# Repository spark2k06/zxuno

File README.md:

# loader128k y 128sna2rom

Cargador de "ROMs" para ZXUno a partir snapshots de 128K, para utilizar desde el menú del firmware. 

Por un lado tenemos el cargador loader128k, que se autocopia en la VRAM para despues pasar el control al mismo. 

Desde la VRAM se mueven todos los bloques de 16Kb al lugar que les corresponde, se restauran los registros y por último se 

pasa el control al PC del Snapshot.

128sna2rom por su parte se utiliza para crear la "ROM" parcheando datos de loader128k.

Idea desarrollada a partir del siguiente hilo con ayuda de Antonio Villena y el emulador ZEsarUX de Cesar Hernández:

http://www.zxuno.com/forum/viewtopic.php?f=12&t=530

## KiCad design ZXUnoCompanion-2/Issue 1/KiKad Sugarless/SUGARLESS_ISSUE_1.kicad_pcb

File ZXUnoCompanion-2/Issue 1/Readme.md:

Propuestas para una hipotética Issue 2, para quién se atreva con ella :-):

- LLevar todos los pines disponibles de Atmega128 o Arduino Mega 2560 a un único conector, a modo de expansión.

- Corregir pinout ISP del atmega128 para evitar tener que hacer fix si se quiere usar éste. Se trata de los pines MOSI y MISO, que actualmente no están donde corresponden.

- Añadir chip CH340 para poder programar el atmega128 por serie como la versión del arduino mega, en lugar de sólo por ISP, y llevar pos pistas las señales del CH340 a los pines D+ y D- del conector de arduino, para que también pueda ser programado desde el conector microUSB sin necesidad de abrir la carcasa.

- ¿Otras?

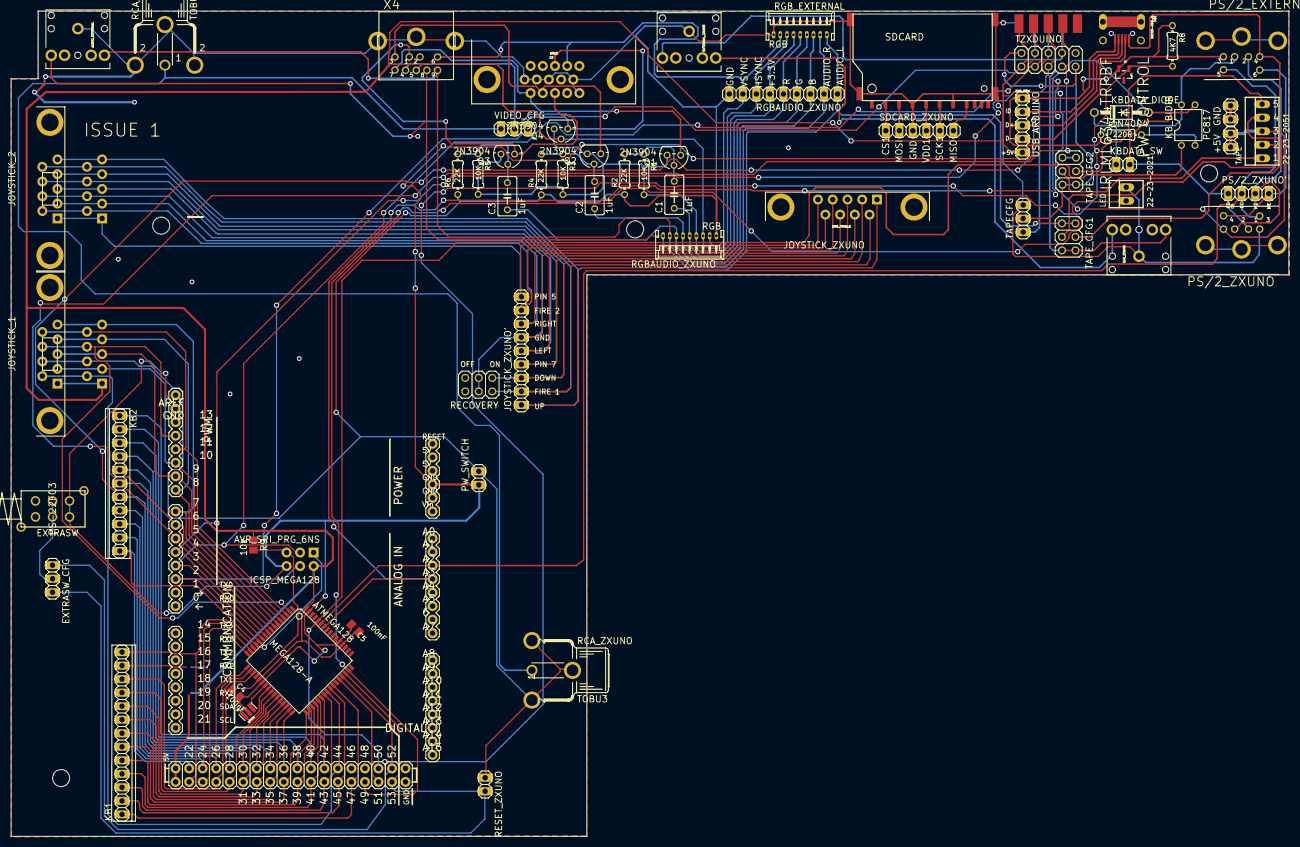
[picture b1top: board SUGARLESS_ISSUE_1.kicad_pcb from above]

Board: 2 copper layers, 240.0 x 155.0 mm, 68 parts (0 on the bottom side), 98 nets.

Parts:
+5V: 1X02
@HOLE0, @HOLE1, @HOLE2, @HOLE3: (no value)
ARDUINO_MEGA: ARDUINO_MEGA_R3FULL; ARDUINO_MEGA
ATMEGA128: MEGA128-A; TQFP64
AUDIO_EXTERNAL: AUDIO-JACK
C1, C2, C3: 1uF; C050-035X075
C4, C5: 100nF; C0805K
EAR_ZXUNO: AUDIO-JACK
EXTERNAL_ZXUNO: AUDIO-JACK
EXTRASW: PS-22F03
EXTRASW_CFG: 1X03
GND: 1X02
ICSP_MEGA128: AVR_SPI_PRG_6NS; 2X3-NS
JOYSTICK_1, JOYSTICK_2: DB9_MALE
JOYSTICK_ZXUNO: DB9_FEMALE; DB9
JOYSTICK_ZXUNO': 1X09
KB1: 1X13
KB2: 1X11
KBDATA_DIODE: 1N4004; DO41-10
KBDATA_SW: 1X02
KB_BIDIR: PC817; DIL04
LED: 22-23-2021
PS/2_EXTERNAL, PS/2_ZXUNO: M_DIN6
PS/2_ZXUNO': 1X04
PW_CONTROL: IRLML6344TRPBF; SOT95P240X112-3N
PW_SWITCH: 1X02
Q1, Q2, Q3, Q4: 2N3904; TO92
R1, R3, R5: 10K; 0204%2f7
R2, R4, R6: 22K; 0204%2f7
R7: 220R; 0204%2f7
R8: 4K7; 0204%2f7
R9: 10k; M0805
RCA_EXTERNAL: TOBU3
RCA_ZXUNO: TOBU3
RECOVERY: 2X03
RESET_ZXUNO: 1X02
RGBAUDIO_ZXUNO: RGB; 53048-09
RGBAUDIO_ZXUNO': 1X09
RGB_EXTERNAL: RGB; 53048-09
SDCARD: SDCMF-10915W010
SDCARD_ZXUNO: 1X06
TAPE: 22-23-2051
TAPECFG: 1X03
TAPE_CFG1, TAPE_CFG2: 2X03
TZXDUINO: 2X05
U$1: MICRO-USB-B; MICRO_USB_4_LEGS
USB_ARDUINO: 1X05
VIDEO_CFG: 1X03
X3: DB15
X4: M_DIN9
X5: F09D
Y1: 16MHz; RESONATOR

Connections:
+3.3V: Q1.1, Q2.1, Q3.1, Q4.1, R1.2, R3.2, R5.2, RGBAUDIO_ZXUNO.6, RGBAUDIO_ZXUNO'.6, RGB_EXTERNAL.6
+5V: +5V.1, +5V.2, ARDUINO_MEGA.5V@1, ARDUINO_MEGA.5V@2, ATMEGA128.21, ATMEGA128.52, ATMEGA128.64, C4.1, C5.1, ICSP_MEGA128.2, JOYSTICK_1.5, JOYSTICK_1.14, PS/2_EXTERNAL.4, PS/2_ZXUNO.4, R9.1, TAPE.3, TZXDUINO.1, U$1.VCC, USB_ARDUINO.5, X4.2, X5.1
AUDIO_L: AUDIO_EXTERNAL.TIP, RGBAUDIO_ZXUNO.1, RGBAUDIO_ZXUNO'.1, RGB_EXTERNAL.1, TAPE_CFG1.1, TAPE_CFG1.2, X4.8
AUDIO_R: AUDIO_EXTERNAL.RING, RGBAUDIO_ZXUNO.2, RGBAUDIO_ZXUNO'.2, RGB_EXTERNAL.2, X4.9
B: C3.1, RGBAUDIO_ZXUNO.3, RGBAUDIO_ZXUNO'.3, RGB_EXTERNAL.3
BOUT: Q3.3, X3.3, X4.1
COMPOSITE: RCA_EXTERNAL.1, RCA_ZXUNO.1, VIDEO_CFG.1
CS1: SDCARD.1, SDCARD_ZXUNO.1
CSYNC: Q4.3, VIDEO_CFG.3, X3.13
D+: U$1.D+, USB_ARDUINO.3
D-: U$1.D-, USB_ARDUINO.4
EXTRA: ARDUINO_MEGA.52, ATMEGA128.45, EXTRASW_CFG.1
G: C2.1, RGBAUDIO_ZXUNO.4, RGBAUDIO_ZXUNO'.4, RGB_EXTERNAL.4
GND: GND.1, GND.2, JOYSTICK_1.8, JOYSTICK_1.17, LED.2, PS/2_ZXUNO.3, PW_CONTROL.3, PW_SWITCH.2, R2.1, R4.1, R6.1, RCA_EXTERNAL.2, RCA_EXTERNAL.2@1, RCA_EXTERNAL.2@2, RCA_ZXUNO.2, RCA_ZXUNO.2@1, RCA_ZXUNO.2@2, RESET_ZXUNO.1, RGBAUDIO_ZXUNO.9, RGBAUDIO_ZXUNO'.9, RGB_EXTERNAL.9, SDCARD.3, SDCARD.6, SDCARD.M1, SDCARD.M2, SDCARD.M3, SDCARD.M4, SDCARD_ZXUNO.3, TAPECFG.3, X3.5, X3.6, X3.7, X3.8, X3.10, X4.SH1, X4.SH2, X4.SH3, X5.5, X5.6
GND_POW: ATMEGA128.22, ATMEGA128.53, ATMEGA128.63, C4.2, C5.2, EXTRASW.5, EXTRASW.6, ICSP_MEGA128.6, PS/2_EXTERNAL.3, PW_CONTROL.2, PW_SWITCH.1, R7.1, R8.1, TAPECFG.1, U$1.GND, USB_ARDUINO.1, Y1.2
GND_TAPE: TAPECFG.2, TAPE_CFG2.5, TAPE_CFG2.6, TZXDUINO.2, TZXDUINO.9
GOUT: Q2.3, X3.2, X4.3
HSYNC: Q4.2, RGBAUDIO_ZXUNO.7, RGBAUDIO_ZXUNO'.7, RGB_EXTERNAL.7, X4.5
ID: U$1.ID, USB_ARDUINO.2
IN_L: EAR_ZXUNO.TIP, EXTERNAL_ZXUNO.TIP, TAPE_CFG1.5, TAPE_CFG1.6, TZXDUINO.8, X5.9
IN_R: EAR_ZXUNO.RING, EXTERNAL_ZXUNO.RING
JOY2PS2_1: ARDUINO_MEGA.7, ATMEGA128.7, JOYSTICK_1.1, JOYSTICK_1.10
JOY2PS2_2: ARDUINO_MEGA.8, ATMEGA128.6, JOYSTICK_1.2, JOYSTICK_1.11
JOY2PS2_3: ARDUINO_MEGA.9, ATMEGA128.5, JOYSTICK_1.3, JOYSTICK_1.12
JOY2PS2_4: ARDUINO_MEGA.10, ATMEGA128.4, JOYSTICK_1.4, JOYSTICK_1.13
JOY2PS2_6: ARDUINO_MEGA.11, ATMEGA128.3, JOYSTICK_1.6, JOYSTICK_1.15
JOY2PS2_7: ARDUINO_MEGA.12, ATMEGA128.2, JOYSTICK_1.7, JOYSTICK_1.16
JOY2PS2_9: ARDUINO_MEGA.44, ATMEGA128.40, JOYSTICK_1.9, JOYSTICK_1.18
JOYZXUNO_1: JOYSTICK_2.1, JOYSTICK_2.10, JOYSTICK_ZXUNO.1, JOYSTICK_ZXUNO'.1
JOYZXUNO_2: JOYSTICK_2.2, JOYSTICK_2.11, JOYSTICK_ZXUNO.2, JOYSTICK_ZXUNO'.3, RECOVERY.1
JOYZXUNO_3: JOYSTICK_2.3, JOYSTICK_2.12, JOYSTICK_ZXUNO.3, JOYSTICK_ZXUNO'.5
JOYZXUNO_4: JOYSTICK_2.4, JOYSTICK_2.13, JOYSTICK_ZXUNO.4, JOYSTICK_ZXUNO'.7
JOYZXUNO_5: JOYSTICK_2.5, JOYSTICK_2.14, JOYSTICK_ZXUNO.5, JOYSTICK_ZXUNO'.9
JOYZXUNO_6: JOYSTICK_2.6, JOYSTICK_2.15, JOYSTICK_ZXUNO.6, JOYSTICK_ZXUNO'.2, RECOVERY.2
JOYZXUNO_7: JOYSTICK_2.7, JOYSTICK_2.16, JOYSTICK_ZXUNO.7, JOYSTICK_ZXUNO'.4
JOYZXUNO_8: JOYSTICK_2.8, JOYSTICK_2.17, JOYSTICK_ZXUNO.8, JOYSTICK_ZXUNO'.6, RECOVERY.3, RECOVERY.4
JOYZXUNO_9: JOYSTICK_2.9, JOYSTICK_2.18, JOYSTICK_ZXUNO.9, JOYSTICK_ZXUNO'.8
KB_CONTROL: ARDUINO_MEGA.50, ATMEGA128.60, KB_BIDIR.1
M1_KB1: ARDUINO_MEGA.23, ATMEGA128.14, KB1.13
M1_KB2: ARDUINO_MEGA.25, ATMEGA128.16, KB1.12
M1_KB3: ARDUINO_MEGA.27, ATMEGA128.18, KB1.11
M1_KB4: ARDUINO_MEGA.29, ATMEGA128.25, KB1.10
M1_KB5: ARDUINO_MEGA.31, ATMEGA128.27, KB1.9
M1_KB6: ARDUINO_MEGA.33, ATMEGA128.29, KB1.8
M1_KB7: ARDUINO_MEGA.35, ATMEGA128.31, KB1.7
M1_KB8: ARDUINO_MEGA.37, ATMEGA128.33, KB1.6
M1_KB9: ARDUINO_MEGA.39, ATMEGA128.35, KB1.5
M1_KB10: ARDUINO_MEGA.41, ATMEGA128.37, KB1.4
M1_KB11: ARDUINO_MEGA.43, ATMEGA128.39, KB1.3
M1_KB12: ARDUINO_MEGA.45, ATMEGA128.41, KB1.2
M1_KB13: ARDUINO_MEGA.47, ATMEGA128.42, KB1.1
M2_KB1: ARDUINO_MEGA.22, ATMEGA128.13, ICSP_MEGA128.1, KB2.11
M2_KB2: ARDUINO_MEGA.24, ATMEGA128.15, KB2.10
M2_KB3: ARDUINO_MEGA.26, ATMEGA128.17, KB2.9
M2_KB4: ARDUINO_MEGA.28, ATMEGA128.19, KB2.8
M2_KB5: ARDUINO_MEGA.30, ATMEGA128.26, KB2.7
M2_KB6: ARDUINO_MEGA.32, ATMEGA128.28, KB2.6
M2_KB7: ARDUINO_MEGA.34, ATMEGA128.30, KB2.5
M2_KB8: ARDUINO_MEGA.36, ATMEGA128.32, KB2.4
M2_KB9: ARDUINO_MEGA.38, ATMEGA128.34, KB2.3
M2_KB10: ARDUINO_MEGA.40, ATMEGA128.36, KB2.2
M2_KB11: ARDUINO_MEGA.42, ATMEGA128.38, KB2.1
MISO1: SDCARD.7, SDCARD_ZXUNO.6
MOSI1: SDCARD.2, SDCARD_ZXUNO.2
unnamed: VIDEO_CFG.2, X4.4
unnamed: PS/2_ZXUNO.SH1, PS/2_ZXUNO.SH2, PS/2_ZXUNO.SH3
unnamed: PS/2_EXTERNAL.SH1, PS/2_EXTERNAL.SH2, PS/2_EXTERNAL.SH3
unnamed: C1.2, Q1.2, R1.1, R2.2
unnamed: KB_BIDIR.2, R7.2
unnamed: ATMEGA128.23, Y1.3
unnamed: ATMEGA128.24, Y1.1
unnamed: C3.2, Q3.2, R5.1, R6.2
unnamed: C2.2, Q2.2, R3.1, R4.2
N/C: TAPE_CFG2.1, TAPE_CFG2.2
PS2_KBCLK: ARDUINO_MEGA.A2, ATMEGA128.59, PS/2_EXTERNAL.5, PS/2_ZXUNO.5, PS/2_ZXUNO'.2
PS2_KBDATA: ARDUINO_MEGA.A3, ATMEGA128.58, KBDATA_DIODE.A, KBDATA_SW.2, KB_BIDIR.3, PS/2_ZXUNO.1, PS/2_ZXUNO'.1
PS2_KBDATA': KBDATA_DIODE.C, KBDATA_SW.1, KB_BIDIR.4, PS/2_EXTERNAL.1
PS2_MSCLK: PS/2_EXTERNAL.6, PS/2_ZXUNO.6, PS/2_ZXUNO'.4
PS2_MSDATA: PS/2_EXTERNAL.2, PS/2_ZXUNO.2, PS/2_ZXUNO'.3
PW_CONTROL: ARDUINO_MEGA.51, ATMEGA128.44, PW_CONTROL.1, R8.2
PW_LED: ARDUINO_MEGA.49, ATMEGA128.47, LED.1
R: C1.1, RGBAUDIO_ZXUNO.5, RGBAUDIO_ZXUNO'.5, RGB_EXTERNAL.5
RESET: ARDUINO_MEGA.53, ATMEGA128.46, EXTRASW_CFG.3, RESET_ZXUNO.2
ROUT: Q1.3, X3.1, X4.7
RST: ATMEGA128.20, ICSP_MEGA128.5, R9.2
SCK1: SDCARD.5, SDCARD_ZXUNO.5
SWITCH: EXTRASW.3, EXTRASW.4, EXTRASW_CFG.2
TAPE_1: TAPE.1, TAPE_CFG2.3
TAPE_2: TAPE.2, TAPE_CFG1.3
TAPE_4: TAPE.4, TAPE_CFG1.4
TAPE_5: TAPE.5, TAPE_CFG2.4
TZX_DOWN: ARDUINO_MEGA.4, ATMEGA128.10, TZXDUINO.5, X5.3
TZX_PLAY: ARDUINO_MEGA.5, ATMEGA128.9, TZXDUINO.6, X5.8
TZX_ROOT: ARDUINO_MEGA.2, ATMEGA128.12, ICSP_MEGA128.4, TZXDUINO.3, X5.2
TZX_STOP: ARDUINO_MEGA.6, ATMEGA128.8, TZXDUINO.7, X5.4
TZX_UP: ARDUINO_MEGA.3, ATMEGA128.11, ICSP_MEGA128.3, TZXDUINO.4, X5.7
VDD1: SDCARD.4, SDCARD_ZXUNO.4
VSYNC: RGBAUDIO_ZXUNO.8, RGBAUDIO_ZXUNO'.8, RGB_EXTERNAL.8, X3.14, X4.6

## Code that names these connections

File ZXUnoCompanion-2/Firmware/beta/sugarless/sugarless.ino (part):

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void TZXDUINO_pushbutton(uint8_t pin, uint8_t bcd)
{
	// Pulsa
	pinPut(TZX_ROOT_PIN, TZX_ROOT_BCD, LO);
	pinSet(TZX_ROOT_PIN, TZX_ROOT_BCD, _OUT);
	
	// Delay de 250 ms
	_delay_ms(250);

	// Suelta
	pinSet(TZX_ROOT_PIN, TZX_ROOT_BCD, _IN);
	pinPut(TZX_ROOT_PIN, TZX_ROOT_BCD, HI);

}

//Inicializar TZXDUINO
void TZXDUINOInit()
{
	pinSet(TZX_ROOT_PIN, TZX_ROOT_BCD, _IN);
	pinPut(TZX_ROOT_PIN, TZX_ROOT_BCD, HI);

	pinSet(TZX_UP_PIN, TZX_UP_BCD, _IN);
	pinPut(TZX_UP_PIN, TZX_UP_BCD, HI);

	pinSet(TZX_DOWN_PIN, TZX_DOWN_BCD, _IN);
	pinPut(TZX_DOWN_PIN, TZX_DOWN_BCD, HI);

	pinSet(TZX_PLAY_PIN, TZX_PLAY_BCD, _IN);
	pinPut(TZX_PLAY_PIN, TZX_PLAY_BCD, HI);

	pinSet(TZX_STOP_PIN, TZX_STOP_BCD, _IN);
	pinPut(TZX_STOP_PIN, TZX_STOP_BCD, HI);
}

//Inicializar Matriz
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
	fnpulsada = 0; //Se pone a 0 la pulsacion de una tecla de funcion
	
	if (pinStat(SYSTEM_PIN, SYSTEM_BCD)) // Gestion del switch SYSTEM (RESET)
	{
		_delay_us(10); //debounce
		if (pinStat(SYSTEM_PIN, SYSTEM_BCD))
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		
		if (matriz[Z_V_ROW][C_COL] & 0x01) // UP
		{
			TZXDUINO_pushbutton(TZX_UP_PIN, TZX_UP_BCD); 
			matriz[Z_V_ROW][C_COL] = 0;
		}

		if (matriz[Z_V_ROW][V_COL] & 0x01) // DOWN
		{
			TZXDUINO_pushbutton(TZX_DOWN_PIN, TZX_DOWN_BCD);
			matriz[Z_V_ROW][V_COL] = 0;
		}

		if (matriz[B_M_ROW][B_COL] & 0x01) // STOP
		{
			TZXDUINO_pushbutton(TZX_STOP_PIN, TZX_STOP_BCD);
			matriz[B_M_ROW][B_COL] = 0;
		}

		if (matriz[B_M_ROW][N_COL] & 0x01) // PLAY
		{
			TZXDUINO_pushbutton(TZX_PLAY_PIN, TZX_PLAY_BCD);
			matriz[B_M_ROW][N_COL] = 0;
		}

		if (matriz[B_M_ROW][M_COL] & 0x01) // ROOT
		{
			TZXDUINO_pushbutton(TZX_ROOT_PIN, TZX_ROOT_BCD);
			matriz[B_M_ROW][M_COL] = 0;
		}

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
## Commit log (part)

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2018-02-24 Issue 1
2018-03-02 Release 7
2018-03-02 Alpha 1
2018-03-10 Alpha 2
2018-03-14 Alpha 3
2018-03-21 Alpha 4
2018-03-28 Beta 1
2018-04-03 Beta 2
2018-04-09 Beta 3
2018-04-10 Beta 4
2018-04-12 Infografia por yoxxxoy
    Infografía de la configuracion de Jumpers por yoxxxoy.
2018-04-12 Infografía por yoxxxoy.
    Infografía de la configuracion de Jumpers por yoxxxoy.
2018-04-12 Infografía por yoxxxoy
    Infografía de la configuracion de Jumpers por yoxxxoy
2018-05-02 Beta 5
2018-05-09 Release 1
2018-05-09 Release 7.1
2018-05-14 Release 1.1
2018-10-08 Release 7.1.1
    Le faltaba un } al último else de la función de setup(), gracias iturbez del foro de zxuno por el aviso.
2018-11-21 Limpieza de repositorio
2018-11-21 Reorganizacion de repositorio
2019-01-12 Release 2
2019-04-20 Release 8
2021-05-19 1.1
    Deteccion correcta la SRAM de 1024KB
2021-05-23 Opción de monocromo (Verde, ámbar y B&W)
2021-05-31 Cambio de paleta monocromática
    Se cambia la paleta de tonalidades monocromáticas para representar mejor los colores brillantes, gracias @desUBIKado por la sugerencia.
2021-06-06 Version alternativa para memoria SRAM externa
    Para sintetizar, adicionalmente se debe deshabilitar los modulos WiFi y MIDI desde el fichero de configuracion common/config.vh
2021-06-08 SAA1099, Control WiFi y Turbo
    Se añade SAA1099, gracias a azesmbog
    Se controla el encendido y apagado de WiFi con F11
    La activación y desactivación del modo Turbo (28 Mhz) con F12 ahora se produce al soltar la tecla, y se mantiene el estado
2021-06-09 SAA1099 y PZX, sin WiFi ni MIDI para SRAM interna
2021-06-09 Opcion de monocromo como modulo opcional
2021-06-13 PZX Loader: Añadir funcionalidad de marca de usuario y rebobinado a esa marca (Contador a 0)
2021-06-13 Cambiado a CTRL-F8 para rewind de fichero y restaurado F9 para STOP
2021-06-13 Actualización de binarios
2021-06-13 Añado la licencia correspondiente
2021-06-21 Version para ZXUncore
    Uso de RGB666 para mejora de la opción monocromática. Ahora se visualiza correctamente incluso en modos de ULA+
2021-08-11 Compatibilidad joysplitter
    Compatibilidad con el puerto 1 del joysplitter de antoniovillena
2021-08-31 ON/OFF WiFi Reset opcional
2021-09-02 Fix to lack of sound in some games, by @vanfanel
2021-09-08 Merge with version "multi" of ZXUno SVN repository
    Merge with the latest version of the ZXUno SVN repository, which has settings with different settings:
    * Simple Joystick
    * Double Joystick (Jamma or Version 2M by ManuFerHi)
    * JoySplitter by Antonio Villena
2021-10-07 Joystick splitter support
2021-10-08 Correccion a #3: Si el splitter está desactivado o no esta presente por la compilacion condicional, la linea fire3 se deja a 1 para solventar problemas con mandos de megadrive.
2021-11-14 PZX hasta 216KB con SRAM de 512KB
    Cuando el core se usa con 512KB de SRAM, la carga del PZX se lleva a cabo mediante los bancos 13,14,15,22,23,24,25,26,27,28,29,30,31 y 8Kb del banco 12, lo que nos ofrece un total de 216KB.
2022-02-02 Cambios JoySplitter y MonochromeRGB en ZXUnCore
    * Uso del bit 5 del DEVCTRL2 para el JoySplitter
    * Mejora del modulo de MonochromeRGB en la version ZXUnCore, gracias a Fernando Mosquera (@benitoss)
2022-02-02 Fix binarios SPECTRUM.ZX1
    Actualización de los binarios de Spectrum, los había subido con más tamaño del debido.
2022-02-03 Soporte del segundo disparo en JoyKB
    Se añade soporte del segundo botón de disparo en el Joystick de teclado:
    KEYPAD 0 o cualquiera de las teclas de Menú de Windows.
2022-02-04 Correcciones y mejoras
    * Correcciones del Splitter DB9
    * Soporte para segundo puerto de Joystick
2022-02-05 Rollback del modulo SPI a la version de Julio2020
    Identificado el problema de error cargando CPM, se procede a realizar un rollback. Si se encuentra la causa del fallo en el modulo, se volverá a actualizar corrigiendolo.
2022-02-08 Reset de teclado al inicio del core
    Se estable un reset de teclado para forzar el establecimiento del SET 2, solo al inicio del core, no en un reset, master-reset, hard-reset, etc...
    Esta característica es útil para no tener que desconectar el ZXUno después del uso del core de PCXT, el cual establece el SET 1 de ScanCodes. De esta forma, será posible volver al core de Spectrum me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
    Las versiones de memoria externa y vga2m no se actualizan, debido a que no cabe manteniendo sus características de lector de PZX y sonido SAA, que son más importantes. No obstante, cualquiera puede r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
2022-02-24 Frame timing is slightly out of sync with the NES frame by 2 clocks here we take back 1 clock each from line 480 and 500, which are off screen and corrects the slight error. Also position of backporc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
2022-02-24 Removed commented out code
2022-02-25 Actualizacion de binarios
    * Bug fix VGA (by @ZXMicroJack)
    * Unificación de binarios. Ahora se mantiene una única versión para memoria interna, compatible con los modelos de 512Kb y 2Mb.
2022-04-04 Inidicador de actividad WiFi (OSD)
2022-08-04 Added Covox Soundrive support Added Timex joystick support Added Timex AY ports support
2022-08-05 Actualizacion de binarios
2022-08-05 Fix border chane when writting AY registers
2022-08-05 Actualizacion de binarios y configuracion de VGA2M
2022-08-06 Correccion de video cuando no esta activo WiFi OSD
2022-08-21 Nuevo proyecto vgawifi
2022-09-24 root mode removed
2022-09-24 fixing tildes
2022-09-25 Update binaries
2024-06-19 Small Revision
    Small Revision
